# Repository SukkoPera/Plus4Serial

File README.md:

# Plus4Serial
Plus4Serial is an Open Hardware Serial Port Adapter that plugs into the Commodore Plus/4 User Port, turning it into a fully-functional [RS-232 interface](https://en.wikipedia.org/wiki/RS-232).

## Summary
The Plus/4 User Port has all the signals required by an RS-232 interface, but they are at TTL voltage levels (i.e.: 0/+5V). In order to turn them into a real RS-232 port, they need to be shifted to higher voltages, which is the purpose of this board.

All the signals available on the DE-9 port are translated and usable: `RXD`, `TXD`, `RTS`, `CTS`, `DTR`, `DSR` and `DCD`. The only exception is `RI` (Ring Indicator), which is left unconnected.

The board plugs in the User Port, which means that it can also be used on a C16 or C116 through [a User Port card](https://github.com/SukkoPera/16up).

## Notes
This board uses a MAX238 chip for the level shifting, which is nice because it only needs a +5VDC voltage supply. The 9VAC supply available on the User Port is therefore not used. You can find used ones from China easily and cheaply.

If you have an older version of the board with a `CTS/_CTS` jumper, place it in the `_CTS` position, as it's the only correct one.

If you are looking for a terminal emulator, I recommend [Term-80](https://plus4world.powweb.com/software/Term-80_English) as it is hands down the most feature-rich program of its kind (Hint: press <kbd>CBM+H</kbd> when you get lost) and supports communication at 19200 bps (Take that, C64!).

## Releases
If you want to get this board produced, you are recommended to get [the latest release](https://github.com/SukkoPera/Plus4Serial/releases) rather than the current git version, as the latter might be under development and is not guaranteed to be working.

Every release is accompanied by its Bill Of Materials (BOM) file and any relevant notes about it, which you are recommended to read carefully.

## License
The Plus4Serial documentation, including the design itself, is copyright &copy; SukkoPera 2022 and is licensed under the [Creative Commons Attribution-NonCommercial-ShareAlike 4.0 International License](https://creativecommons.org/licenses/by-nc-sa/4.0/).

This documentation is distributed *as is* and WITHOUT ANY EXPRESS OR IMPLIED WARRANTIES whatsoever with respect to its functionality, operability or use, including, without limitation, any implied warranties OF MERCHANTABILITY, SATISFACTORY QUALITY, FITNESS FOR A PARTICULAR PURPOSE or infringement. We expressly disclaim any liability whatsoever for any direct, indirect, consequential, incidental or special damages, including, without limitation, lost revenues, lost profits, losses resulting from business interruption or loss of data, regardless of the form of action or legal theory under which the liability may be asserted, even if advised of the possibility or likelihood of such damages.

## Support the Project
If you want to get some boards manufactured, you can get them from PCBWay through this link:

You get my gratitude and cheap, professionally-made and good quality PCBs, I get some credit that will help with this and [other projects](https://www.pcbway.com/project/member/shareproject/?bmbid=41100). You won't even have to worry about the various PCB options, it's all pre-configured for you!

Also, if you still have to register, [you can use this link](https://www.pcbway.com/setinvite.aspx?inviteid=41100) to get some bonus initial credit (and yield me some more).

You can also buy me a coffee if you want:

## Thanks
* TLC (Levente Hársfalvi) for lots of information about the serial port.
* The 3D model of the User Port connector was grabbed from [GrabCAD](https://grabcad.com/library/commodore-c64-userport-connector-1) but unfortunately the link now seems dead and I don't know who should be credited for it.

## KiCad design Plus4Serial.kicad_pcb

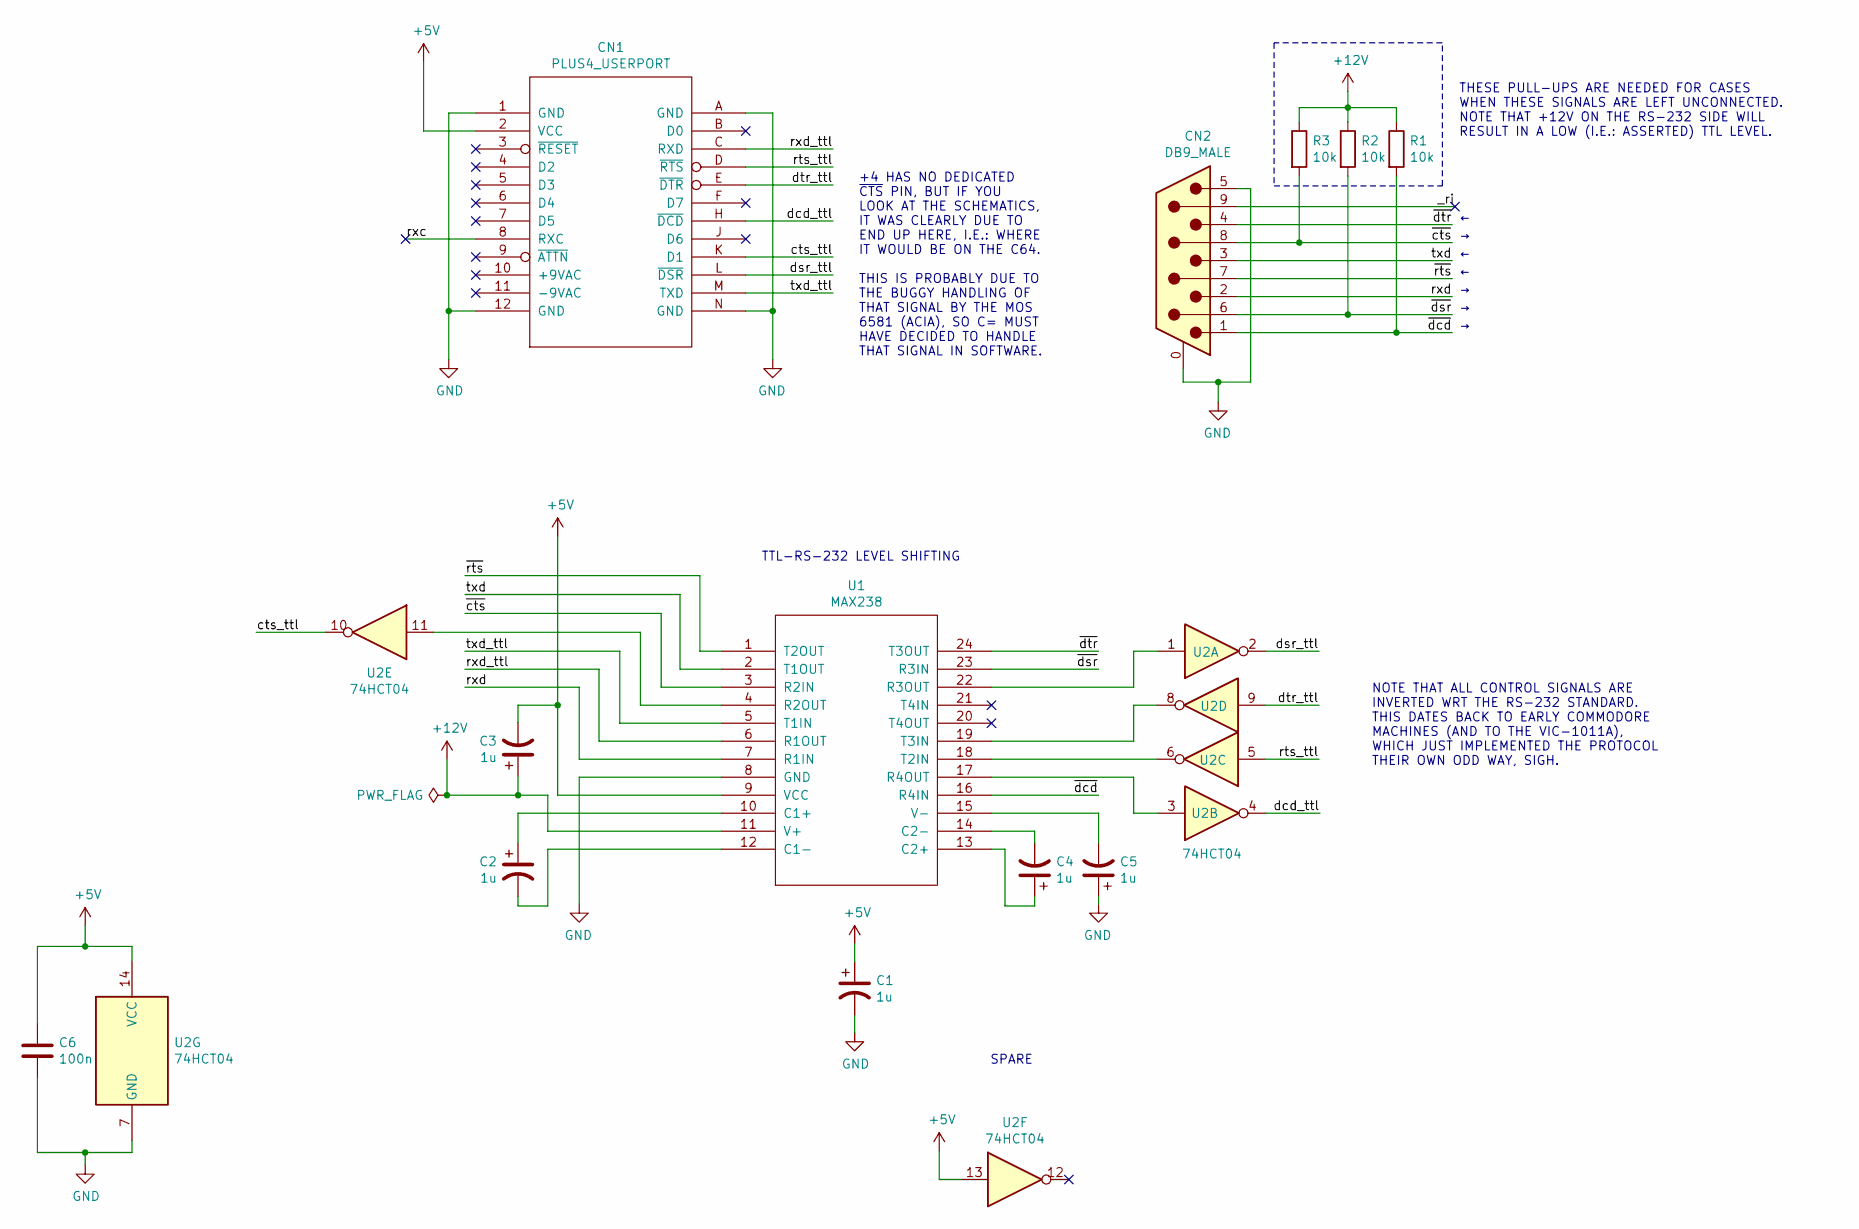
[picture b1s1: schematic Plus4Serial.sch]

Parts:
C1, C2, C3, C4, C5: 1u; CP_Radial_D5.0mm_P2.00mm; MouserPN 710-860010672005
C6: 100n; C_Disc_D7.0mm_W2.5mm_P5.00mm
CN1: PLUS4_USERPORT
CN2: DB9_MALE; DB_9M
R1, R2, R3: 10k; R_Axial_DIN0207_L6.3mm_D2.5mm_P5.08mm_Vertical
U1: MAX238; DIP-24_W7.62mm_Socket_LongPads; MouserPN 700-MAX238ENG+
U2: 74HCT04; DIP-14_W7.62mm_Socket_LongPads; MouserPN 595-SN74HCT04NE4

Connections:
+5V: C1.1, C3.2, C6.1, CN1.2 (VCC), U1.9 (VCC), U2.13, U2.14 (VCC)
+12V: C3.1, R1.1, R2.1, R3.1, U1.11 (V+)
/_ri: CN2.9
/cts_ttl: CN1.K (D1), U2.10
/dcd_ttl: CN1.H (~DCD), U2.4
/dsr_ttl: CN1.L (~DSR), U2.2
/dtr_ttl: CN1.E (~DTR), U2.9
/rts_ttl: CN1.D (~RTS), U2.5
/rxc: CN1.8 (RXC)
/rxd: CN2.2, U1.7 (R1IN)
/rxd_ttl: CN1.C (RXD), U1.6 (R1OUT)
/txd: CN2.3, U1.2 (T1OUT)
/txd_ttl: CN1.M (TXD), U1.5 (T1IN)
/~cts: CN2.8, R3.2, U1.3 (R2IN)
/~dcd: CN2.1, R1.2, U1.16 (R4IN)
/~dsr: CN2.6, R2.2, U1.23 (R3IN)
/~dtr: CN2.4, U1.24 (T3OUT)
/~rts: CN2.7, U1.1 (T2OUT)
GND: C1.2, C5.1, C6.2, CN1.1 (GND), CN1.12 (GND), CN1.A (GND), CN1.N (GND), CN2.0 (PAD), CN2.5, U1.8 (GND), U2.7 (GND)
unnamed: C2.1, U1.10 (C1+)
unnamed: C2.2, U1.12 (C1-)
unnamed: C4.1, U1.13 (C2+)
unnamed: C4.2, U1.14 (C2-)
unnamed: C5.2, U1.15 (V-)
unnamed: U1.4 (R2OUT), U2.11
unnamed: U1.17 (R4OUT), U2.3
unnamed: U1.18 (T2IN), U2.6
unnamed: U1.19 (T3IN), U2.8
unnamed: U1.22 (R3OUT), U2.1

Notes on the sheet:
+4 HAS NO DEDICATED ~CTS~ PIN, BUT IF YOU LOOK AT THE SCHEMATICS, IT WAS CLEARLY DUE TO END UP HERE, I.E.: WHERE IT WOULD BE ON THE C64. THIS IS PROBABLY DUE TO THE BUGGY HANDLING OF THAT SIGNAL BY THE MOS 6581 (ACIA), SO C= MUST HAVE DECIDED TO HANDLE THAT SIGNAL IN SOFTWARE.
SPARE
NOTE THAT ALL CONTROL SIGNALS ARE INVERTED WRT THE RS-232 STANDARD. THIS DATES BACK TO EARLY COMMODORE MACHINES (AND TO THE VIC-1011A), WHICH JUST IMPLEMENTED THE PROTOCOL THEIR OWN ODD WAY, SIGH.
THESE PULL-UPS ARE NEEDED FOR CASES WHEN THESE SIGNALS ARE LEFT UNCONNECTED. NOTE THAT +12V ON THE RS-232 SIDE WILL RESULT IN A LOW (I.E.: ASSERTED) TTL LEVEL.
TTL-RS-232 LEVEL SHIFTING

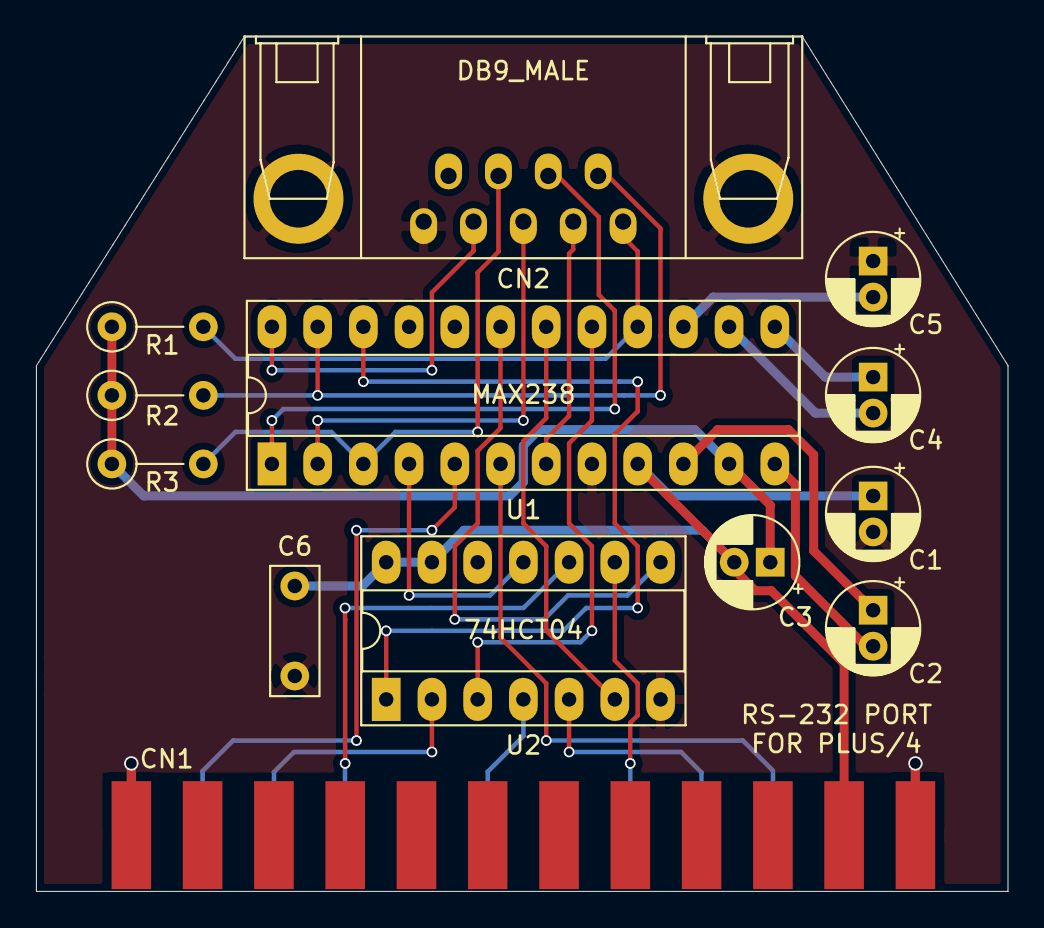
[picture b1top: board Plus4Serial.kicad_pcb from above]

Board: 2 copper layers, 54.0 x 47.5 mm, 13 parts (0 on the bottom side), 27 nets.

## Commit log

2022-02-13 Initial commit, adapter finished, will it work?
2022-09-04 Fix some errors
2022-09-27 Invert signals as per Commodore standard NOTE: PCB not yet updated!
2022-09-28 Erm, fix pull-UPs
2022-09-28 Switch to MAX238
2022-09-28 Take +12V from correct pin
2022-11-01 Remove CTS/_CTS jumper Now we know for certain that CTS is active-high on the User Port
2023-04-07 Add renders and board link
2024-04-06 Add schematics PDF

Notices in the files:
Plus4Serial.kicad_pcb:
CC-BY-NC-SA
© SukkoPera 2022
